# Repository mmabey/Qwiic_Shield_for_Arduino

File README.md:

Qwiic_Shield_for_Arduino
========================================

[*SPX-14201*](https://www.sparkfun.com/products/14286)

Uno compatible shield to connect I2C pins to 4 ports of I2C connectors. Includes level translation.

License Information
-------------------

This product is _**open source**_!

Please review the LICENSE.md file for license information.

If you have any questions or concerns on licensing, please contact techsupport@sparkfun.com.

Distributed as-is; no warranty is given.

- Your friends at SparkFun.

_<COLLABORATION CREDIT>_

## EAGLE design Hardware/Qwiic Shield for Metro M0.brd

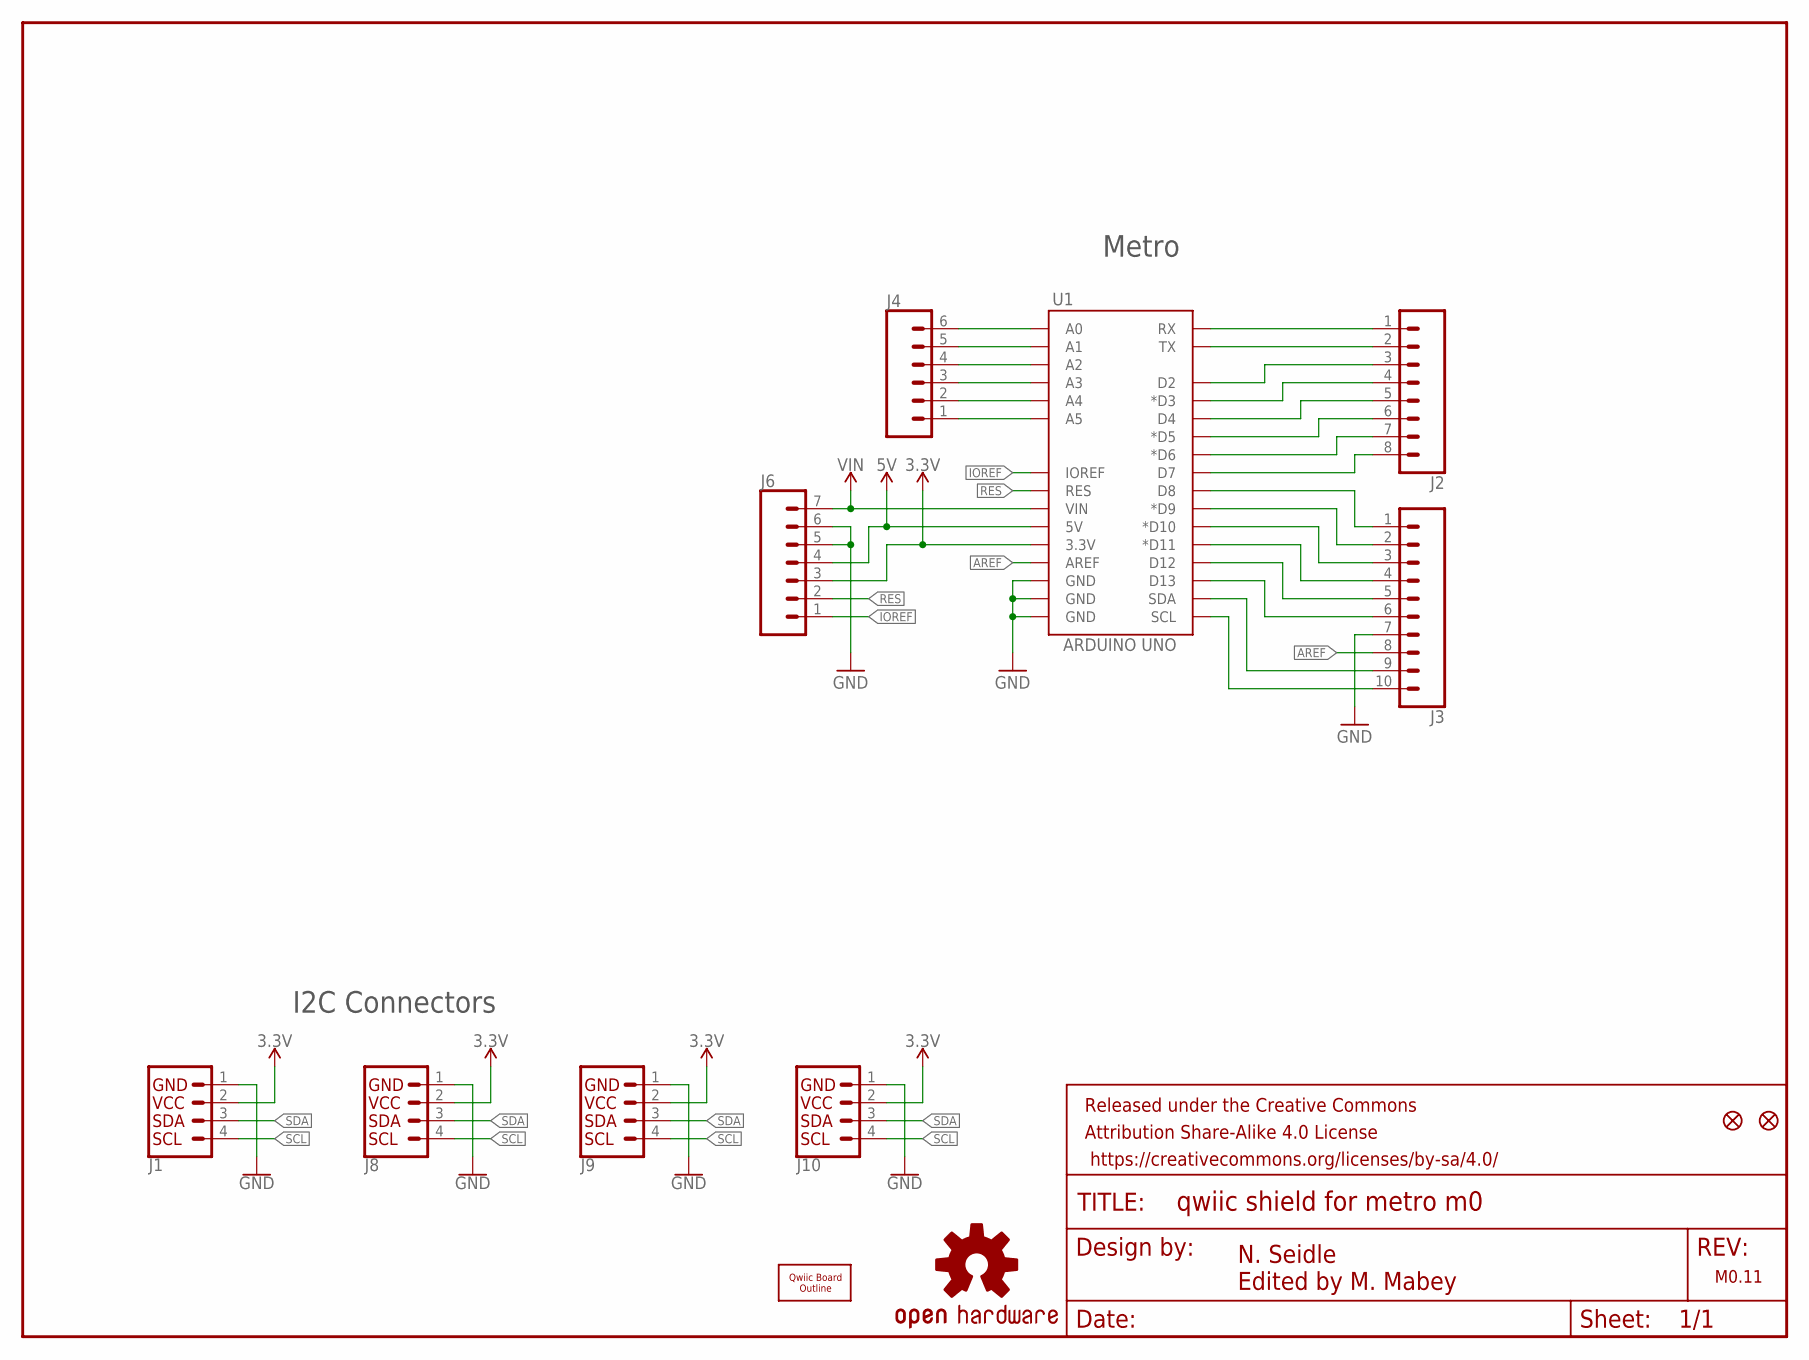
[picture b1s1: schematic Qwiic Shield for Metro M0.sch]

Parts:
FD1, FD2: FIDUCIAL1X2; FIDUCIAL-1X2
FRAME1: FRAME-LETTER; CREATIVE_COMMONS
J1, J8, J9, J10: I2C_STANDARDJS-1MM; 1X04_1MM_RA
J2: CONN_08NO_SILK_FEMALE_PTH; 1X08_NO_SILK
J3: CONN_10NO_SILK_PTH_FEMALE; 1X10_NO_SILK
J4: CONN_06NO_SILK_FEMALE_PTH; 1X06_NO_SILK
J6: CONN_07NO_SILK; 1X07_NO_SILK
LOGO1: OSHW-LOGOMINI; OSHW-LOGO-MINI
U1: ARDUINO UNO; UNO_R3_SHIELD_NOLABELS
U$3: QWIIC_BOARD_OUTLINEH; QWIIC_BOARD_MOUNT_HOLES

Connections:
3.3V: J1.2 (VCC), J6.3, J8.2 (VCC), J9.2 (VCC), J10.2 (VCC), U1.3.3V
5V: J6.4, U1.5V
A0: J4.6, U1.A0
A1: J4.5, U1.A1
A2: J4.4, U1.A2
A3: J4.3, U1.A3
A4: J4.2, U1.A4
A5: J4.1, U1.A5
AREF: J3.8, U1.AREF
D2: J2.3, U1.D2
D3: J2.4, U1.D3 (*D3)
D4: J2.5, U1.D4
D5: J2.6, U1.D5 (*D5)
D6: J2.7, U1.D6 (*D6)
D7: J2.8, U1.D7
D8: J3.1, U1.D8
D9: J3.2, U1.D9 (*D9)
D10: J3.3, U1.D10 (*D10)
D11: J3.4, U1.D11 (*D11)
D12: J3.5, U1.D12
D13: J3.6, U1.D13
GND: J1.1 (GND), J3.7, J6.5, J6.6, J8.1 (GND), J9.1 (GND), J10.1 (GND), U1.GND@0 (GND), U1.GND@1 (GND), U1.GND@2 (GND)
IOREF: J6.1, U1.IOREF
RES: J6.2, U1.RES
RX: J2.1, U1.RX
SCL: J1.4 (SCL), J3.10, J8.4 (SCL), J9.4 (SCL), J10.4 (SCL), U1.SCL
SDA: J1.3 (SDA), J3.9, J8.3 (SDA), J9.3 (SDA), J10.3 (SDA), U1.SDA
TX: J2.2, U1.TX
VIN: J6.7, U1.VIN

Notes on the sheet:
N. Seidle Edited by M. Mabey
Metro
M0.11
I2C Connectors

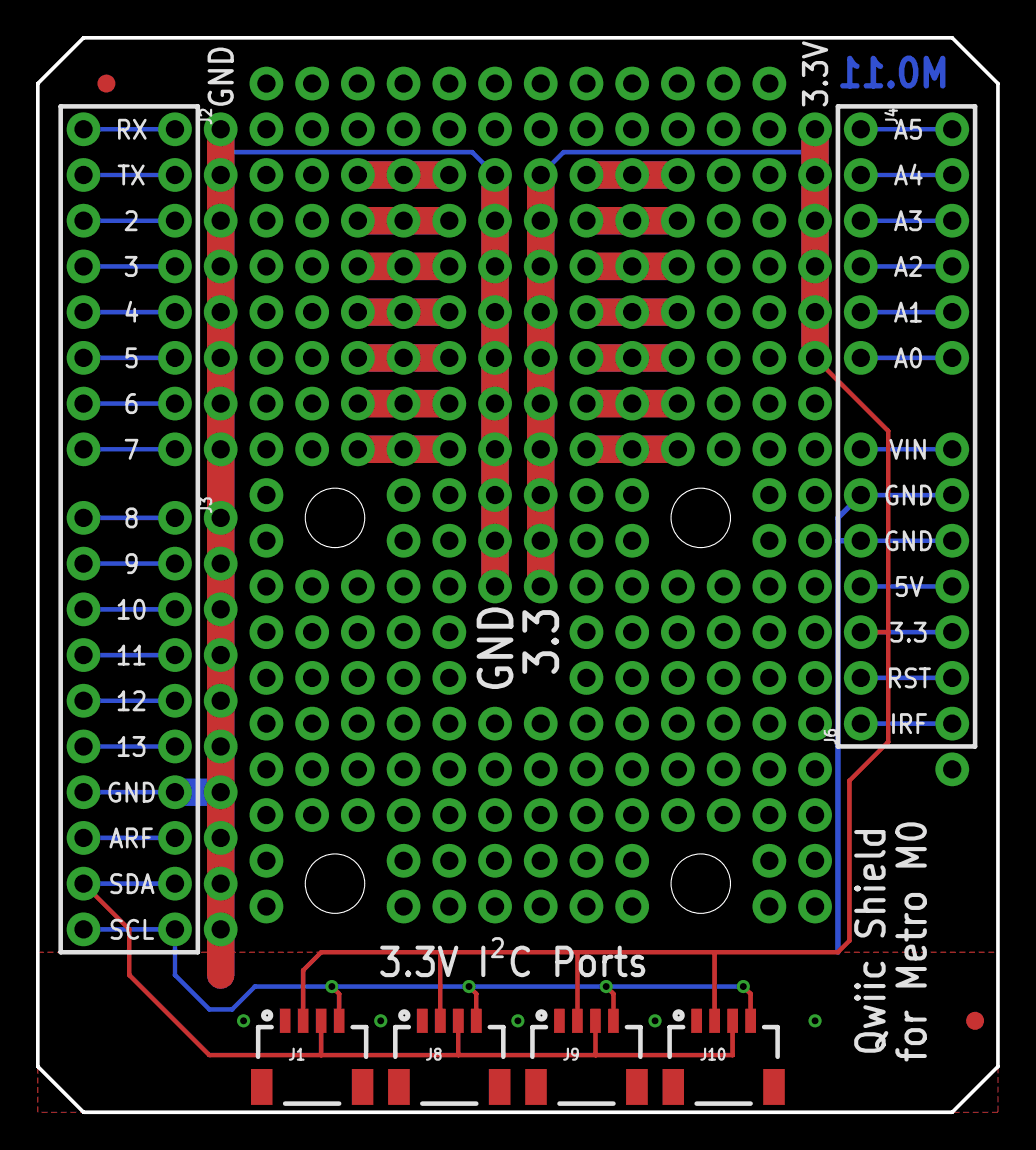
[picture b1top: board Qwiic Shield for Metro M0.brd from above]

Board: 2 copper layers, 53.3 x 59.7 mm, 14 parts (1 on the bottom side), 29 nets.

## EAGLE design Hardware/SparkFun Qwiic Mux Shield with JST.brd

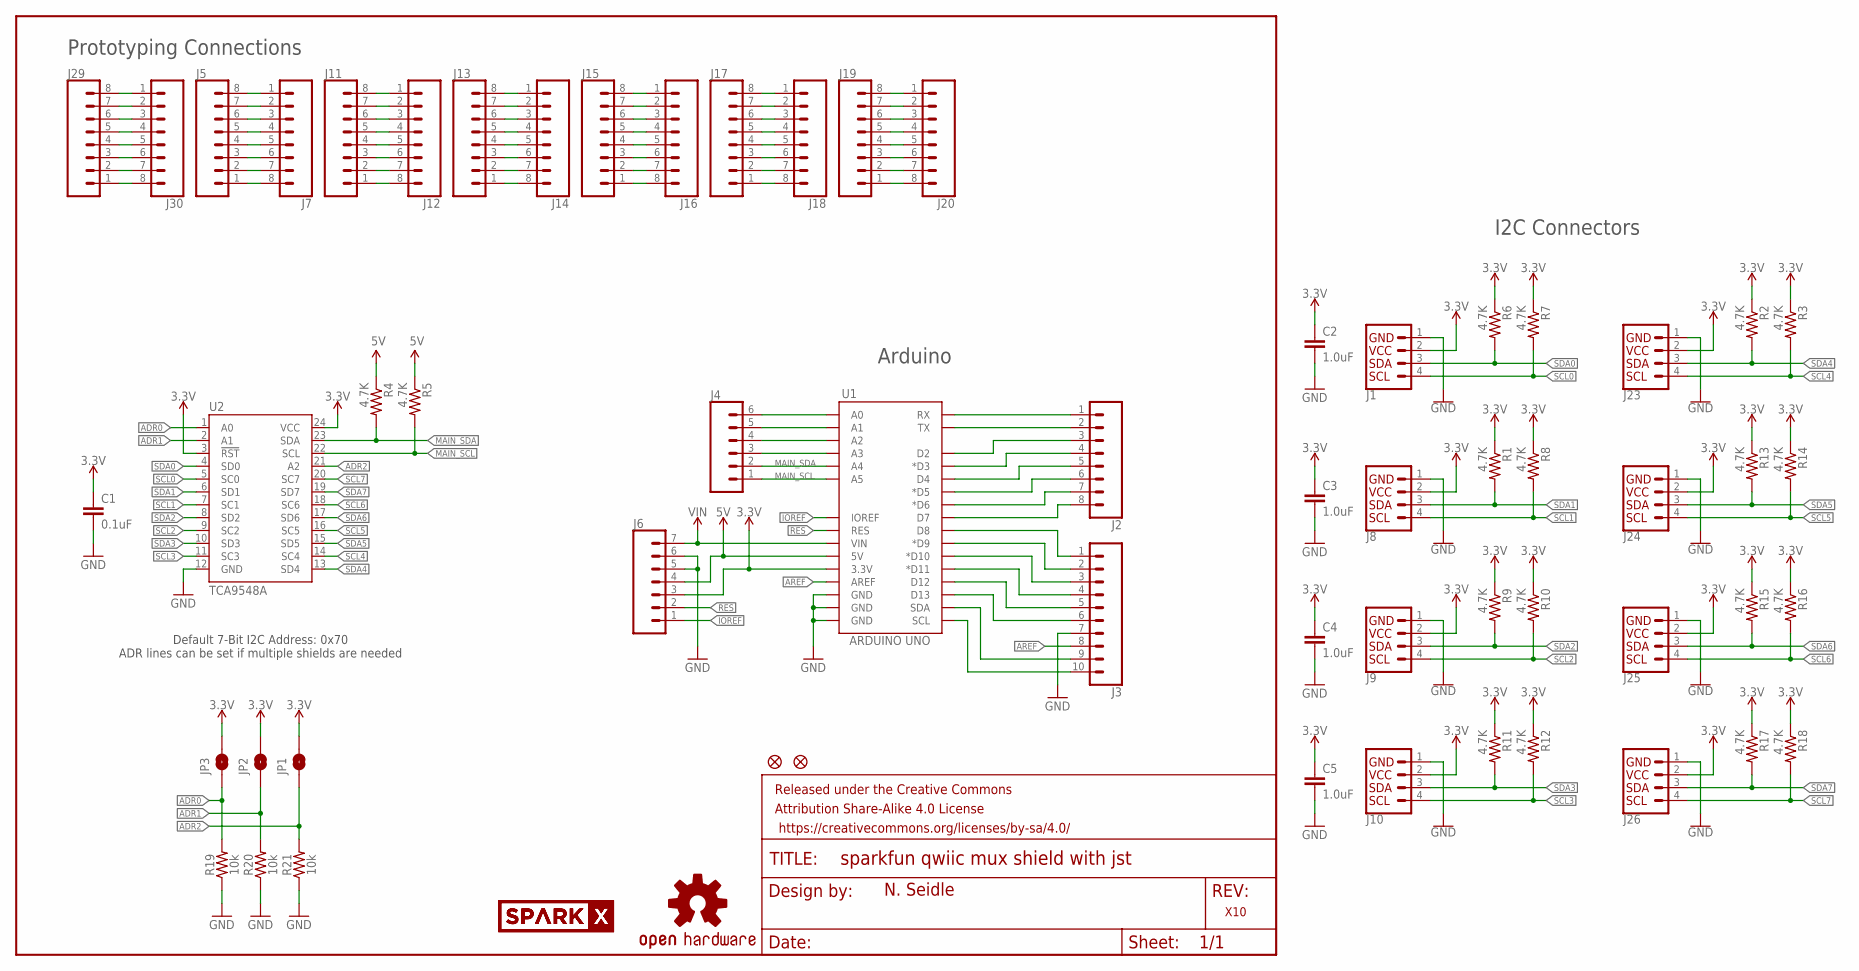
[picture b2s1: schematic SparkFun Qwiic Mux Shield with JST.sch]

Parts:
C1: 0.1uF; 0603
C2, C3, C4, C5: 1.0uF; 0603
FD1, FD2: FIDUCIAL1X2; FIDUCIAL-1X2
FRAME1: FRAME-LETTER; CREATIVE_COMMONS
J1, J8, J9, J10: I2C_STANDARDJS-1MM; 1X04_1MM_RA
J2, J5, J7, J11, J12, J13, J14, J15, J16, J17, J18, J19, J20, J29, J30: CONN_08NO_SILK_FEMALE_PTH; 1X08_NO_SILK
J3: CONN_10NO_SILK_PTH_FEMALE; 1X10_NO_SILK
J4: CONN_06NO_SILK_FEMALE_PTH; 1X06_NO_SILK
J6: CONN_07NO_SILK; 1X07_NO_SILK
J23, J24, J25, J26: I2C_STANDARDSILK; 1X04
JP1, JP2, JP3: JUMPER-SMT_2_NO_SILK; SMT-JUMPER_2_NO_SILK
LOGO1: OSHW-LOGOMINI; OSHW-LOGO-MINI
R1, R2, R3, R4, R5, R6, R7, R8, R9, R10, R11, R12, R13, R14, R15, R16, R17, R18: 4.7K; 0603-RES
R19, R20, R21: 10k; 0603
U1: ARDUINO UNO; UNO_R3_SHIELD_NOLABELS
U2: TCA9548A; TSSOP28
U$1: SPARKX-LOGO3; SPARKX-SMALL
U$2: SPARKX-LOGO5; SPARKX-LARGE

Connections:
5V: J6.4, R4.1, R5.1, U1.5V
A0: J4.6, U1.A0
A1: J4.5, U1.A1
A2: J4.4, U1.A2
A3: J4.3, U1.A3
ADR0: JP3.1, R19.2, U2.1 (A0)
ADR1: JP2.1, R20.2, U2.2 (A1)
ADR2: JP1.1, R21.2, U2.21 (A2)
AREF: J3.8, U1.AREF
D2: J2.3, U1.D2
D3: J2.4, U1.D3 (*D3)
D4: J2.5, U1.D4
D5: J2.6, U1.D5 (*D5)
D6: J2.7, U1.D6 (*D6)
D7: J2.8, U1.D7
D8: J3.1, U1.D8
D9: J3.2, U1.D9 (*D9)
D10: J3.3, U1.D10 (*D10)
D11: J3.4, U1.D11 (*D11)
D12: J3.5, U1.D12
D13: J3.6, U1.D13
GND: C1.2, C2.2, C3.2, C4.2, C5.2, J1.1 (GND), J3.7, J6.5, J6.6, J8.1 (GND), J9.1 (GND), J10.1 (GND), J23.1 (GND), J24.1 (GND), J25.1 (GND), J26.1 (GND), R19.1, R20.1, R21.1, U1.GND@0 (GND), U1.GND@1 (GND), U1.GND@2 (GND), U2.12 (GND)
IOREF: J6.1, U1.IOREF
MAIN_SCL: J4.1, R5.2, U1.A5, U2.22 (SCL)
MAIN_SCL_1: J3.10, U1.SCL
MAIN_SDA: J4.2, R4.2, U1.A4, U2.23 (SDA)
MAIN_SDA_1: J3.9, U1.SDA
unnamed: J5.8, J7.1
unnamed: J5.7, J7.2
unnamed: J5.6, J7.3
unnamed: J5.5, J7.4
unnamed: J5.4, J7.5
unnamed: J5.3, J7.6
unnamed: J5.2, J7.7
unnamed: J5.1, J7.8
unnamed: J11.8, J12.1
unnamed: J11.7, J12.2
unnamed: J11.6, J12.3
unnamed: J11.5, J12.4
unnamed: J11.4, J12.5
unnamed: J11.3, J12.6
unnamed: J11.2, J12.7
unnamed: J11.1, J12.8
unnamed: J13.8, J14.1
unnamed: J13.7, J14.2
unnamed: J13.6, J14.3
unnamed: J13.5, J14.4
unnamed: J13.4, J14.5
unnamed: J13.3, J14.6
unnamed: J13.2, J14.7
unnamed: J13.1, J14.8
unnamed: J15.8, J16.1
unnamed: J15.7, J16.2
unnamed: J15.6, J16.3
unnamed: J15.5, J16.4
unnamed: J15.4, J16.5
unnamed: J15.3, J16.6
unnamed: J15.2, J16.7
unnamed: J15.1, J16.8
unnamed: J17.8, J18.1
unnamed: J17.7, J18.2
unnamed: J17.6, J18.3
unnamed: J17.5, J18.4
unnamed: J17.4, J18.5
unnamed: J17.3, J18.6
unnamed: J17.2, J18.7
unnamed: J17.1, J18.8
unnamed: J19.8, J20.1
unnamed: J19.7, J20.2
unnamed: J19.6, J20.3
unnamed: J19.5, J20.4
unnamed: J19.4, J20.5
unnamed: J19.3, J20.6
unnamed: J19.2, J20.7
unnamed: J19.1, J20.8
unnamed: J29.8, J30.1
unnamed: J29.7, J30.2
unnamed: J29.6, J30.3
unnamed: J29.5, J30.4
unnamed: J29.4, J30.5
unnamed: J29.3, J30.6
unnamed: J29.2, J30.7
unnamed: J29.1, J30.8
RES: J6.2, U1.RES
RX: J2.1, U1.RX
SCL0: J1.4 (SCL), R7.2, U2.5 (SC0)
SCL1: J8.4 (SCL), R8.2, U2.7 (SC1)
SCL2: J9.4 (SCL), R10.2, U2.9 (SC2)
SCL3: J10.4 (SCL), R12.2, U2.11 (SC3)
SCL4: J23.4 (SCL), R3.2, U2.14 (SC4)
SCL5: J24.4 (SCL), R14.2, U2.16 (SC5)
SCL6: J25.4 (SCL), R16.2, U2.18 (SC6)
SCL7: J26.4 (SCL), R18.2, U2.20 (SC7)
SDA0: J1.3 (SDA), R6.2, U2.4 (SD0)
SDA1: J8.3 (SDA), R1.2, U2.6 (SD1)
SDA2: J9.3 (SDA), R9.2, U2.8 (SD2)
SDA3: J10.3 (SDA), R11.2, U2.10 (SD3)
SDA4: J23.3 (SDA), R2.2, U2.13 (SD4)
SDA5: J24.3 (SDA), R13.2, U2.15 (SD5)
SDA6: J25.3 (SDA), R15.2, U2.17 (SD6)
SDA7: J26.3 (SDA), R17.2, U2.19 (SD7)
TX: J2.2, U1.TX
VIN: J6.7, U1.VIN

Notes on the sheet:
N. Seidle
Arduino
X10
Prototyping Connections
I2C Connectors
Default 7-Bit I2C Address: 0x70 ADR lines can be set if multiple shields are needed

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
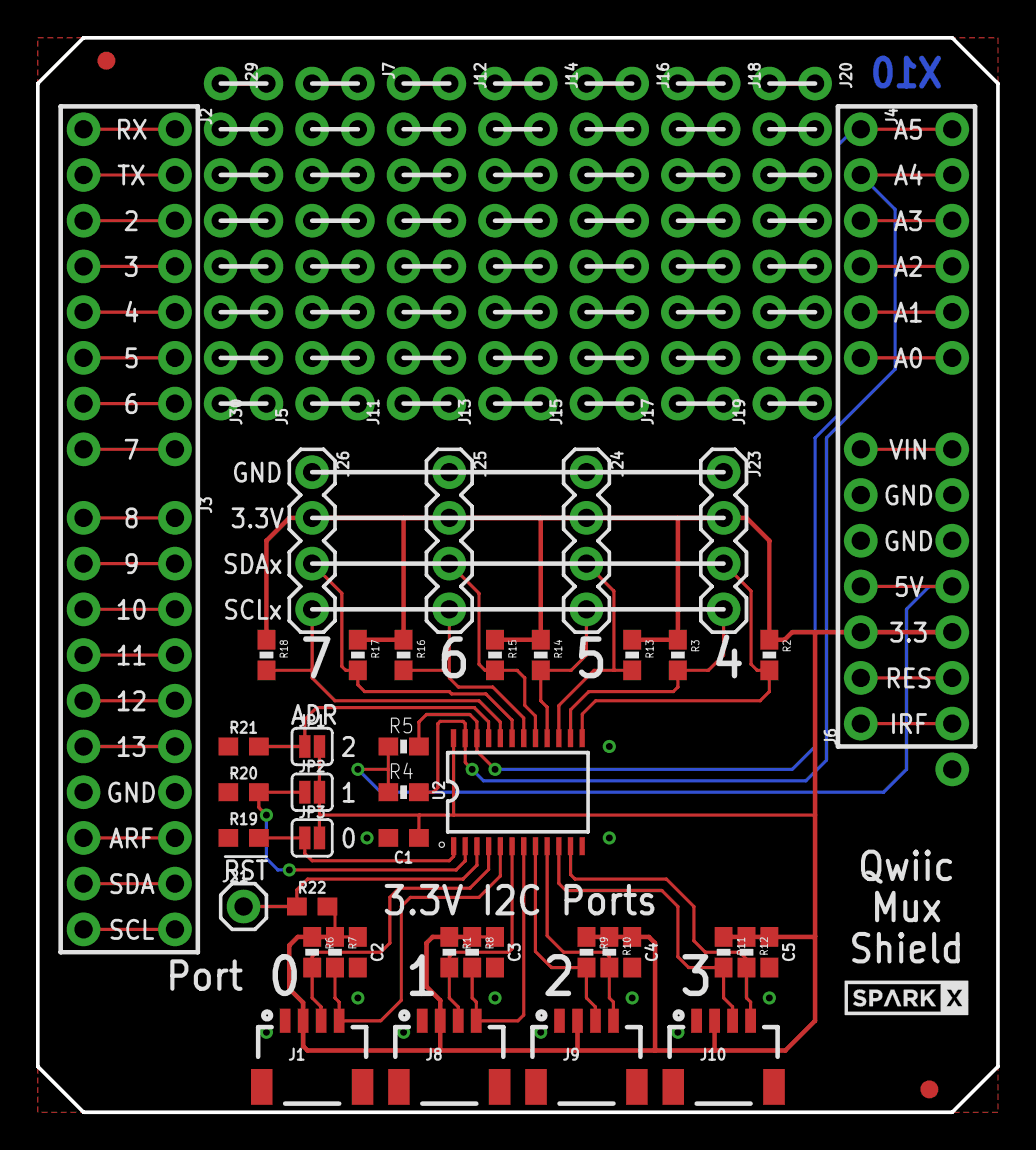
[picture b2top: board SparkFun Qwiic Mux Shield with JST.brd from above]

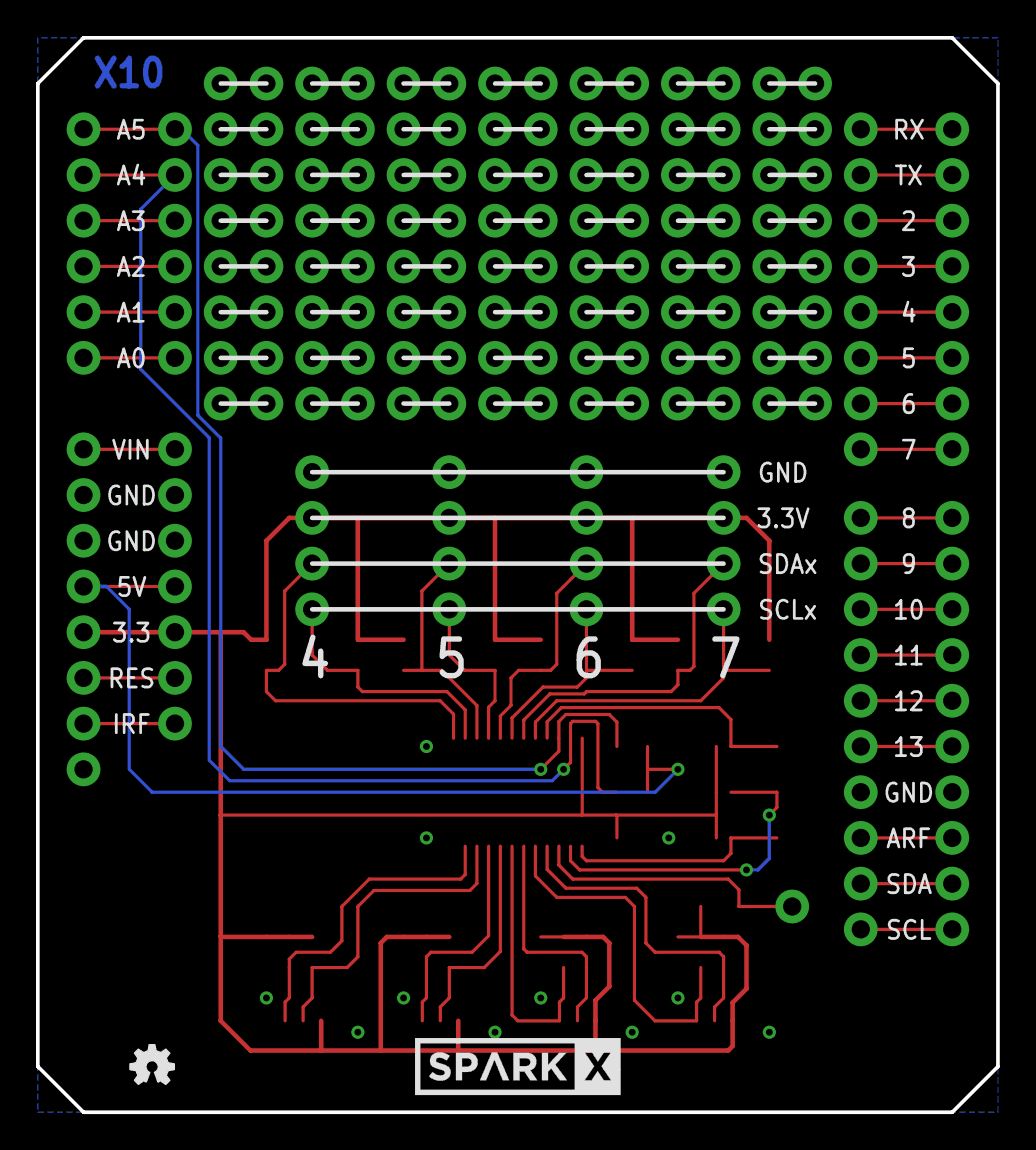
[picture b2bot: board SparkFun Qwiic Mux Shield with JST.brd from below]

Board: 2 copper layers, 53.3 x 59.7 mm, 65 parts (2 on the bottom side), 105 nets.

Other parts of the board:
J21: 1X01
R22: 10k; 0603

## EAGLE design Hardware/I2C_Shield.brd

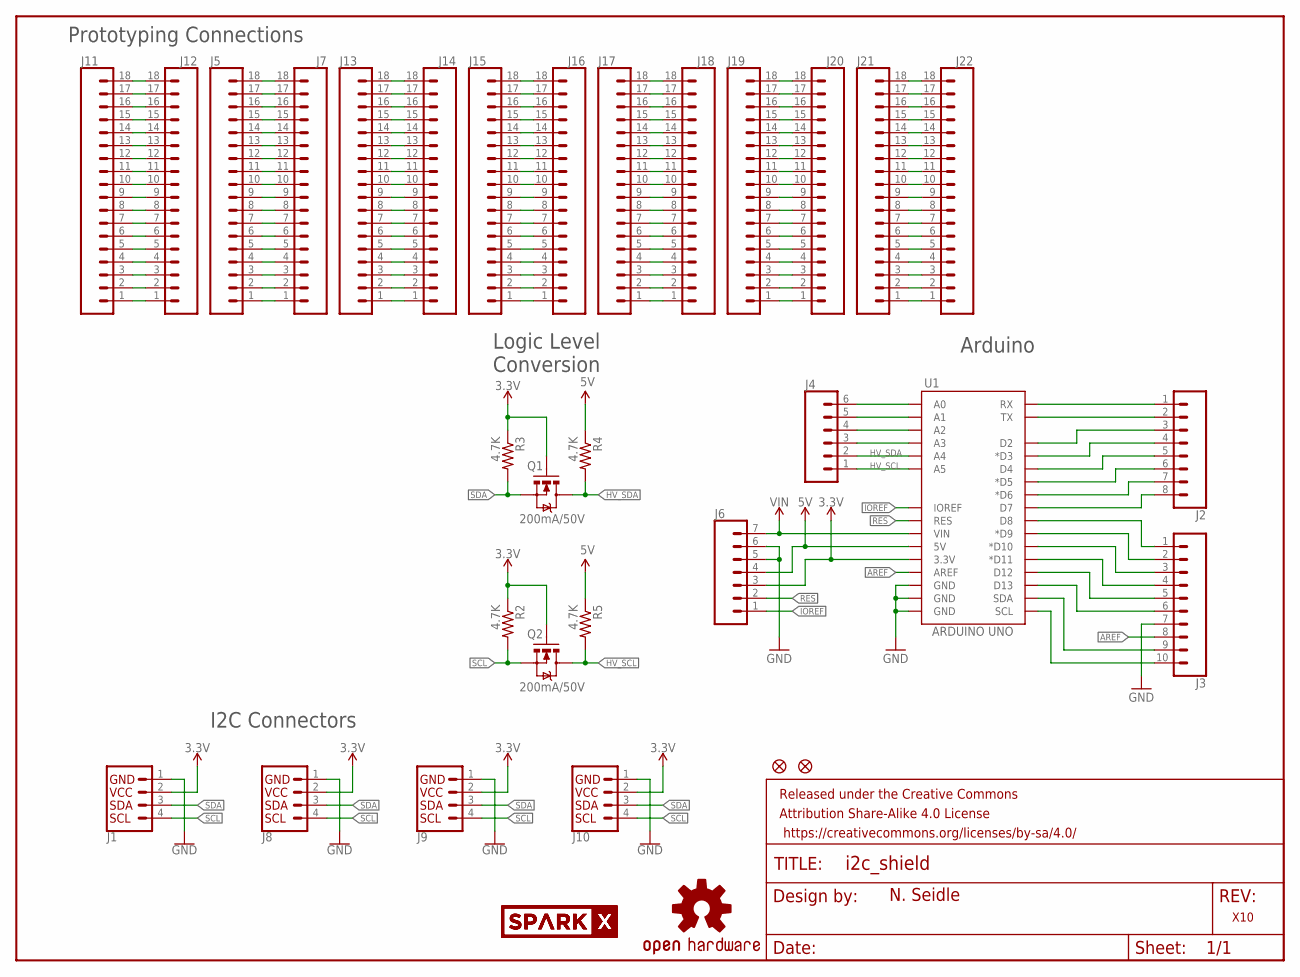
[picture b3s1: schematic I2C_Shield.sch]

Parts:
FD1, FD2: FIDUCIAL1X2; FIDUCIAL-1X2
FRAME1: FRAME-LETTER; CREATIVE_COMMONS
J1, J8, J9, J10: I2C_STANDARDJS-1MM; 1X04_1MM_RA
J2: CONN_08NO_SILK_FEMALE_PTH; 1X08_NO_SILK
J3: CONN_10NO_SILK_PTH_FEMALE; 1X10_NO_SILK
J4: CONN_06NO_SILK_FEMALE_PTH; 1X06_NO_SILK
J5, J7, J11, J12, J13, J14, J15, J16, J17, J18, J19, J20, J21, J22: CONN_18NO_SILK; 1X18_NO_SILK
J6: CONN_07NO_SILK; 1X07_NO_SILK
LOGO1: OSHW-LOGOMINI; OSHW-LOGO-MINI
Q1, Q2: 200mA/50V; SOT23-3
R2, R3, R4, R5: 4.7K; 0603-RES
U1: ARDUINO UNO; UNO_R3_SHIELD_NOLABELS
U$1: SPARKX-LOGO3; SPARKX-SMALL
U$2: SPARKX-LOGO5; SPARKX-LARGE

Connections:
3.3V: J1.2 (VCC), J6.3, J8.2 (VCC), J9.2 (VCC), J10.2 (VCC), Q1.1 (G), Q2.1 (G), R2.1, R3.1, U1.3.3V
5V: J6.4, R4.1, R5.1, U1.5V
A0: J4.6, U1.A0
A1: J4.5, U1.A1
A2: J4.4, U1.A2
A3: J4.3, U1.A3
AREF: J3.8, U1.AREF
D2: J2.3, U1.D2
D3: J2.4, U1.D3 (*D3)
D4: J2.5, U1.D4
D5: J2.6, U1.D5 (*D5)
D6: J2.7, U1.D6 (*D6)
D7: J2.8, U1.D7
D8: J3.1, U1.D8
D9: J3.2, U1.D9 (*D9)
D10: J3.3, U1.D10 (*D10)
D11: J3.4, U1.D11 (*D11)
D12: J3.5, U1.D12
D13: J3.6, U1.D13
GND: J1.1 (GND), J3.7, J6.5, J6.6, J8.1 (GND), J9.1 (GND), J10.1 (GND), U1.GND@0 (GND), U1.GND@1 (GND), U1.GND@2 (GND)
HV_SCL: J4.1, Q2.3 (D), R5.2, U1.A5
HV_SDA: J4.2, Q1.3 (D), R4.2, U1.A4
IOREF: J6.1, U1.IOREF
unnamed: J5.2, J7.2
unnamed: J5.3, J7.3
unnamed: J5.4, J7.4
unnamed: J5.5, J7.5
unnamed: J5.6, J7.6
unnamed: J5.7, J7.7
unnamed: J5.8, J7.8
unnamed: J5.9, J7.9
unnamed: J5.10, J7.10
unnamed: J5.11, J7.11
unnamed: J5.12, J7.12
unnamed: J5.13, J7.13
unnamed: J5.14, J7.14
unnamed: J5.15, J7.15
unnamed: J5.16, J7.16
unnamed: J5.17, J7.17
unnamed: J5.18, J7.18
unnamed: J5.1, J7.1
unnamed: J13.2, J14.2
unnamed: J13.3, J14.3
unnamed: J11.2, J12.2
unnamed: J11.3, J12.3
unnamed: J11.4, J12.4
unnamed: J11.5, J12.5
unnamed: J11.6, J12.6
unnamed: J11.7, J12.7
unnamed: J11.8, J12.8
unnamed: J11.9, J12.9
unnamed: J11.10, J12.10
unnamed: J11.11, J12.11
unnamed: J11.12, J12.12
unnamed: J11.13, J12.13
unnamed: J11.14, J12.14
unnamed: J11.15, J12.15
unnamed: J11.16, J12.16
unnamed: J11.17, J12.17
unnamed: J11.18, J12.18
unnamed: J11.1, J12.1
unnamed: J13.4, J14.4
unnamed: J13.5, J14.5
unnamed: J13.6, J14.6
unnamed: J13.7, J14.7
unnamed: J13.8, J14.8
unnamed: J13.9, J14.9
unnamed: J13.10, J14.10
unnamed: J13.11, J14.11
unnamed: J13.12, J14.12
unnamed: J13.13, J14.13
unnamed: J13.14, J14.14
unnamed: J13.15, J14.15
unnamed: J13.16, J14.16
unnamed: J13.17, J14.17
unnamed: J13.18, J14.18
unnamed: J13.1, J14.1
unnamed: J15.2, J16.2
unnamed: J15.3, J16.3
unnamed: J15.4, J16.4
unnamed: J15.5, J16.5
unnamed: J15.6, J16.6
unnamed: J15.7, J16.7
unnamed: J15.8, J16.8
unnamed: J15.9, J16.9
unnamed: J15.10, J16.10
unnamed: J15.11, J16.11
unnamed: J15.12, J16.12
unnamed: J15.13, J16.13
unnamed: J15.14, J16.14
unnamed: J15.15, J16.15
unnamed: J15.16, J16.16
unnamed: J15.17, J16.17
unnamed: J15.18, J16.18
unnamed: J15.1, J16.1
unnamed: J17.2, J18.2
unnamed: J17.3, J18.3
unnamed: J17.4, J18.4
unnamed: J17.5, J18.5
unnamed: J17.6, J18.6
unnamed: J17.7, J18.7
unnamed: J17.8, J18.8
unnamed: J17.9, J18.9
unnamed: J17.10, J18.10
unnamed: J17.11, J18.11
unnamed: J17.12, J18.12
unnamed: J17.13, J18.13
unnamed: J17.14, J18.14
unnamed: J17.15, J18.15
unnamed: J17.16, J18.16
unnamed: J17.17, J18.17
unnamed: J17.18, J18.18
unnamed: J17.1, J18.1
unnamed: J19.2, J20.2
unnamed: J19.3, J20.3
unnamed: J19.4, J20.4
unnamed: J19.5, J20.5
unnamed: J19.6, J20.6
unnamed: J19.7, J20.7
unnamed: J19.8, J20.8
unnamed: J19.9, J20.9
unnamed: J19.10, J20.10
unnamed: J19.11, J20.11
unnamed: J19.12, J20.12
unnamed: J19.13, J20.13
unnamed: J19.14, J20.14
unnamed: J19.15, J20.15
unnamed: J19.16, J20.16
unnamed: J19.17, J20.17
unnamed: J19.18, J20.18
unnamed: J19.1, J20.1
unnamed: J21.2, J22.2
unnamed: J21.3, J22.3
unnamed: J21.4, J22.4
unnamed: J21.5, J22.5
unnamed: J21.6, J22.6
unnamed: J21.7, J22.7
unnamed: J21.8, J22.8
unnamed: J21.9, J22.9
unnamed: J21.10, J22.10
unnamed: J21.11, J22.11
unnamed: J21.12, J22.12
unnamed: J21.13, J22.13
unnamed: J21.14, J22.14
unnamed: J21.15, J22.15
unnamed: J21.16, J22.16
unnamed: J21.17, J22.17
unnamed: J21.18, J22.18
unnamed: J21.1, J22.1
RES: J6.2, U1.RES
RX: J2.1, U1.RX
SCL: J1.4 (SCL), J8.4 (SCL), J9.4 (SCL), J10.4 (SCL), Q2.2 (S), R2.2
SCL1: J3.10, U1.SCL
SDA: J1.3 (SDA), J8.3 (SDA), J9.3 (SDA), J10.3 (SDA), Q1.2 (S), R3.2
SDA1: J3.9, U1.SDA
TX: J2.2, U1.TX
VIN: J6.7, U1.VIN

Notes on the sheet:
N. Seidle
Logic Level Conversion
Arduino
X10
Prototyping Connections
I2C Connectors

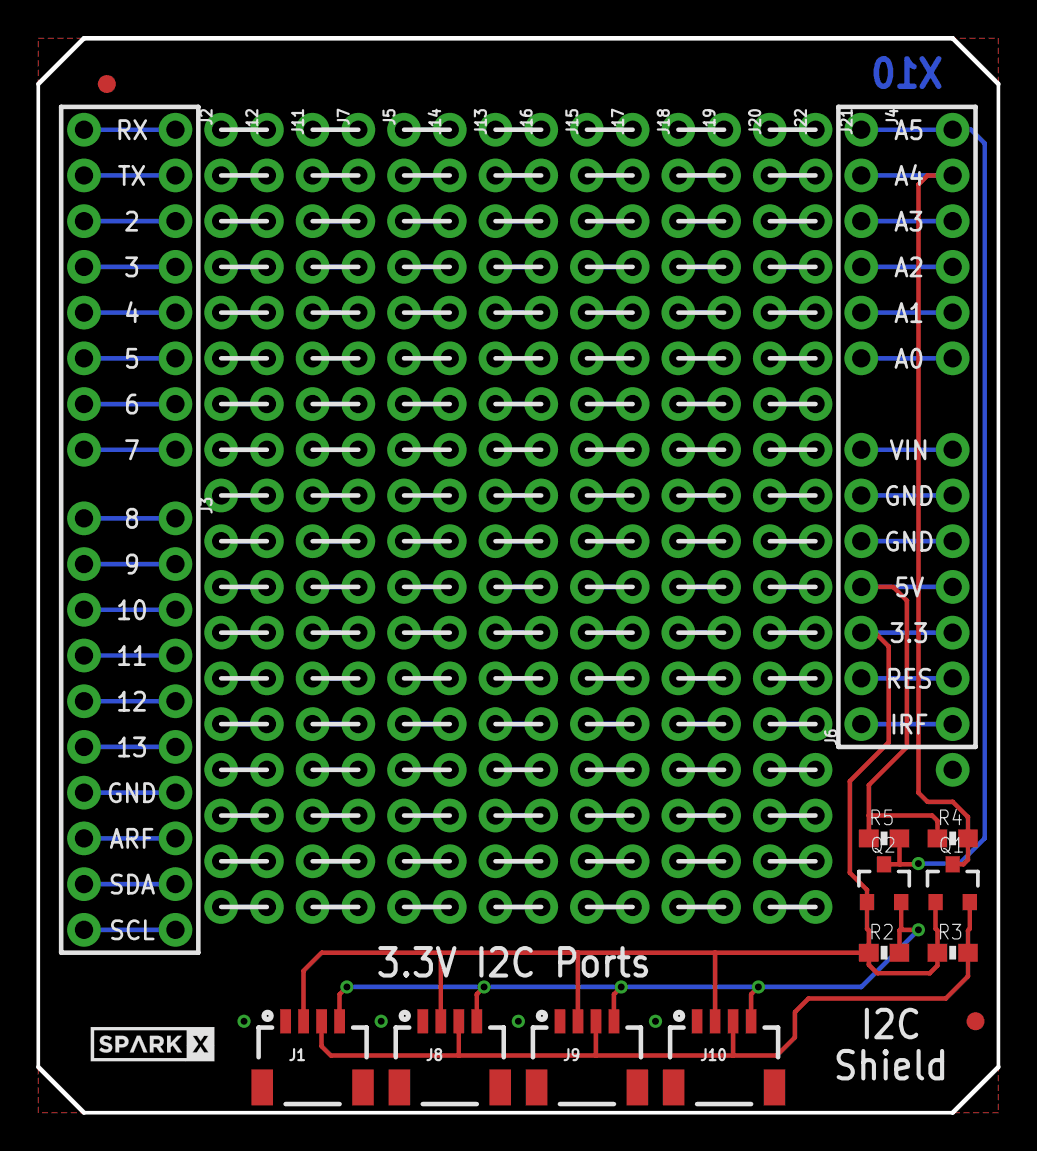
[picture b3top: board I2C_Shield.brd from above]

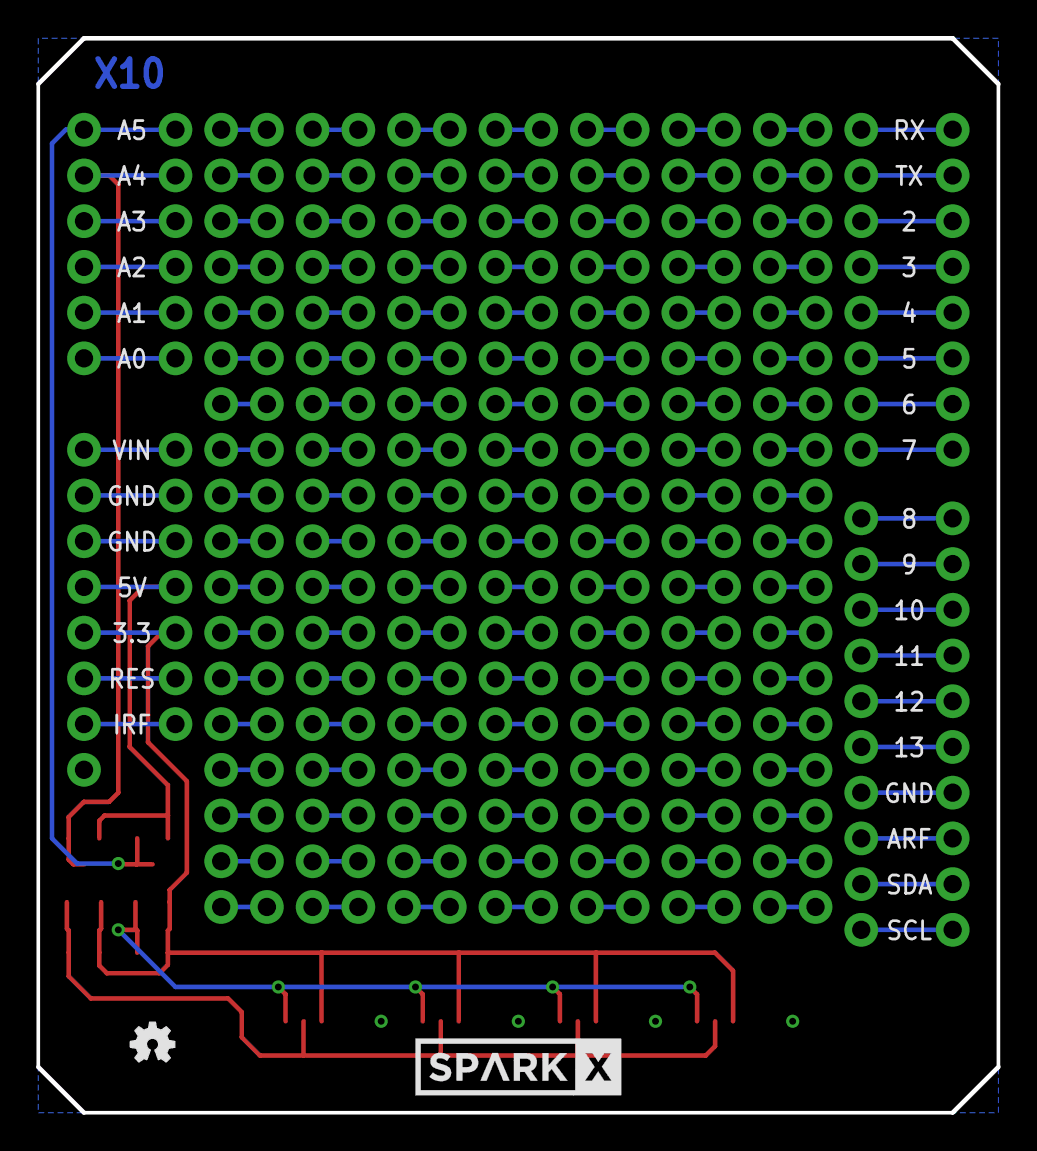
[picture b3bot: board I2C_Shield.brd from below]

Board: 2 copper layers, 53.3 x 59.7 mm, 35 parts (2 on the bottom side), 157 nets.

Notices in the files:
parts and their libraries:
SparkFun-Boards: Licensing: CC v3.0 Share-Alike You are welcome to use this library for commercial purposes.
SparkFun-Aesthetics: Released under the Creative Commons Attribution Share-Alike 4.0 License
SparkFun-Aesthetics: https://creativecommons.org/licenses/by-sa/4.0
